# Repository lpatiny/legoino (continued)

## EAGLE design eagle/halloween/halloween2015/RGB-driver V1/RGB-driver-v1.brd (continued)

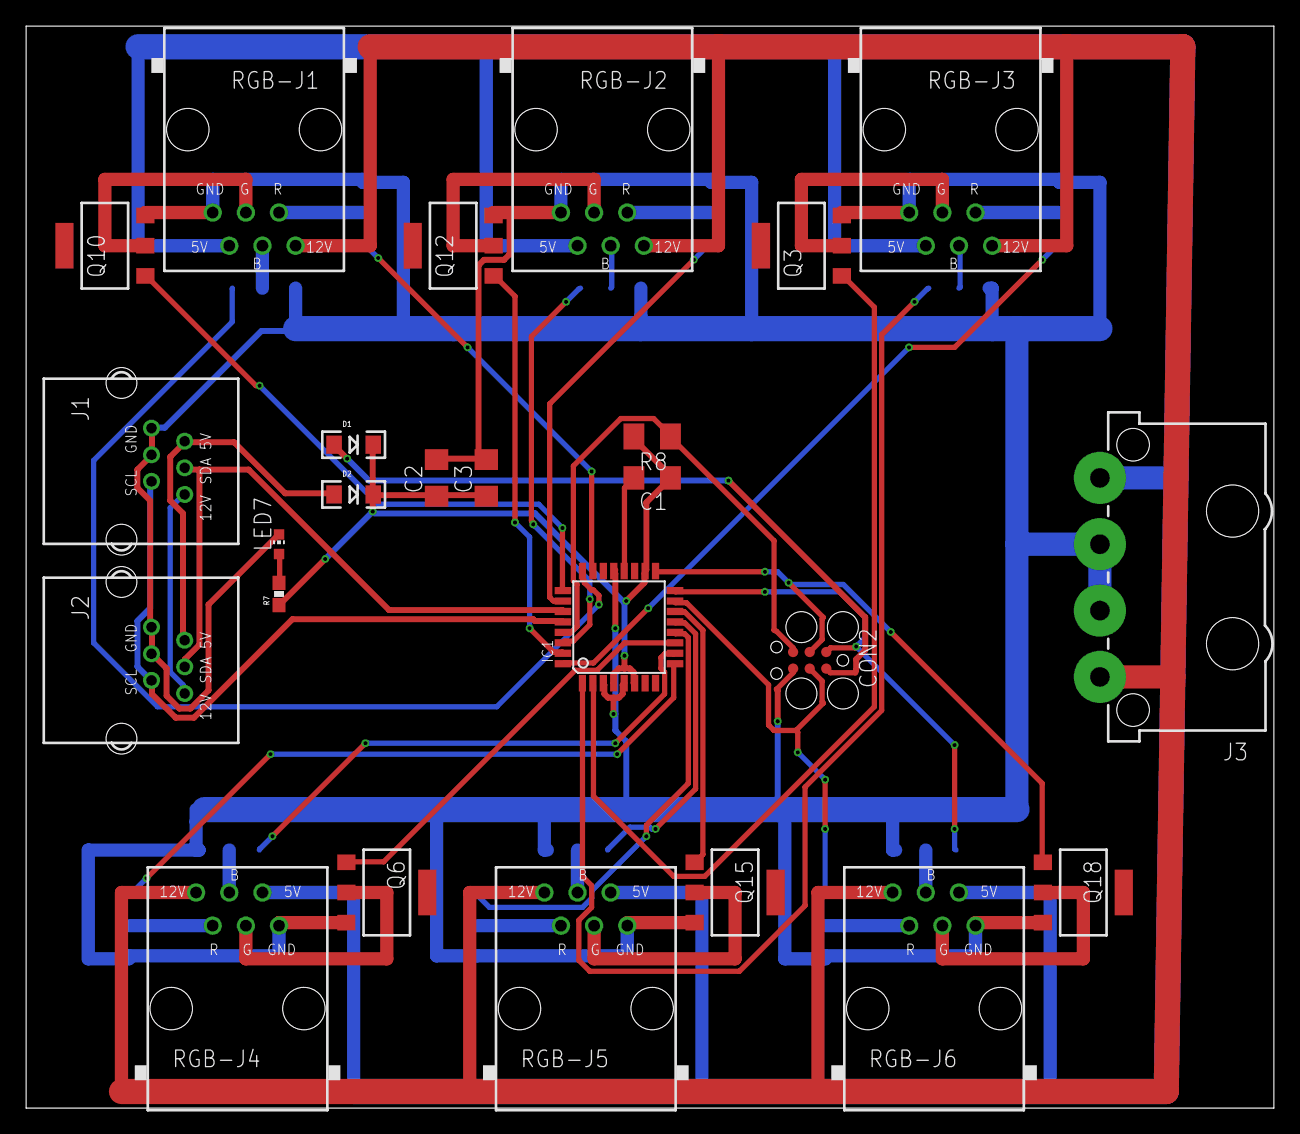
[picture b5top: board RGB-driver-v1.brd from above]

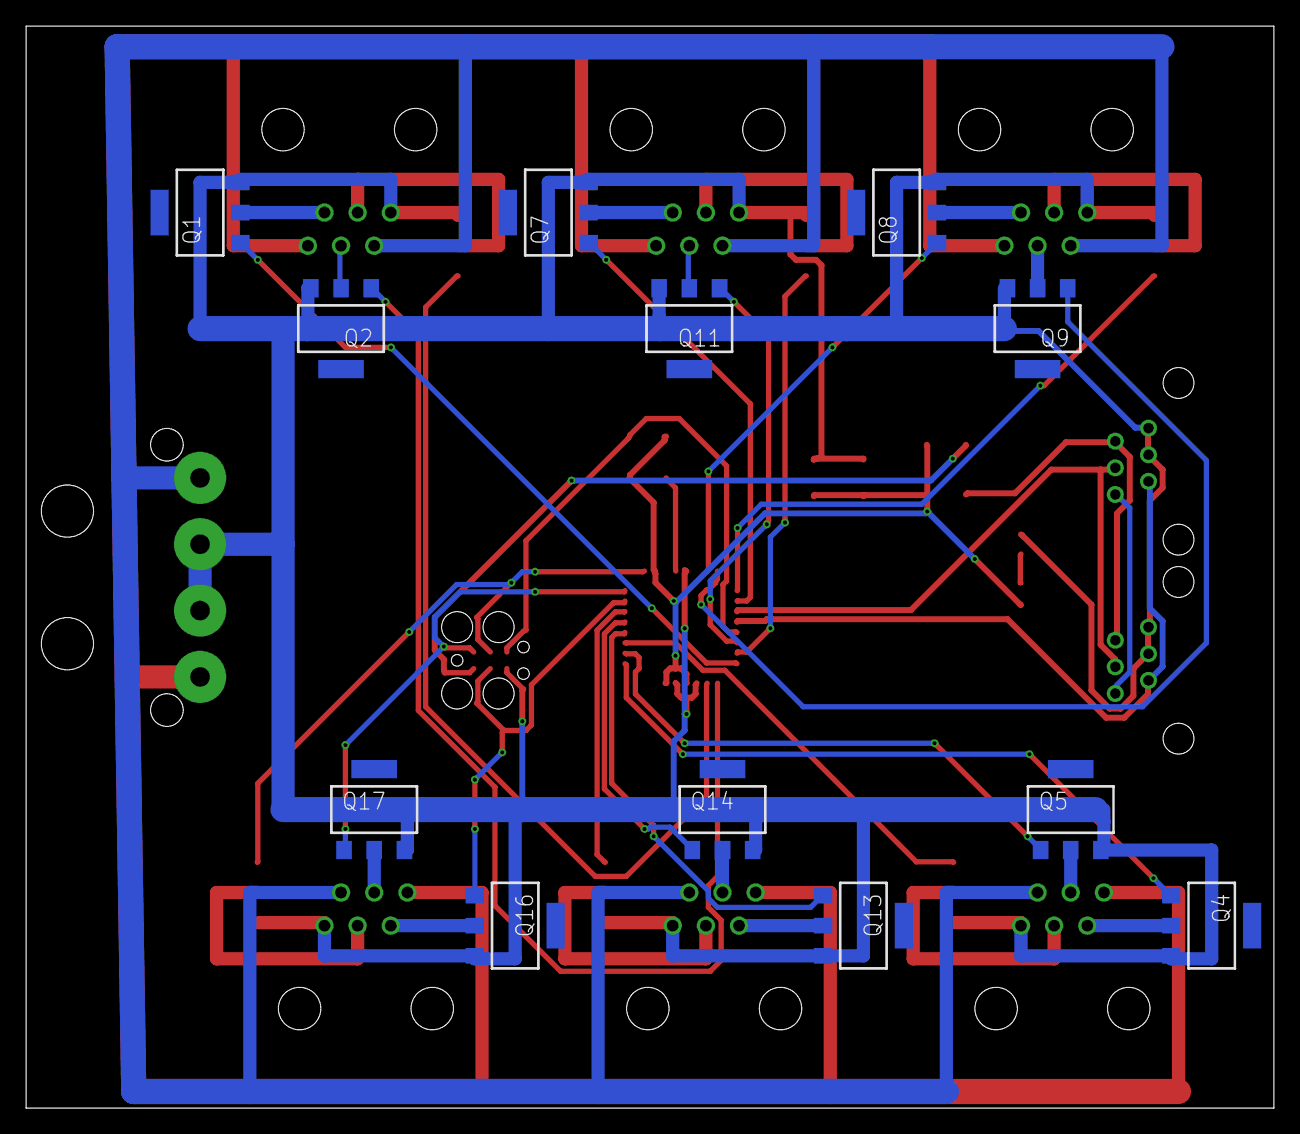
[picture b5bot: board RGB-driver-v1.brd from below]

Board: 2 copper layers, 95.6 x 82.9 mm, 37 parts (12 on the bottom side), 48 nets.

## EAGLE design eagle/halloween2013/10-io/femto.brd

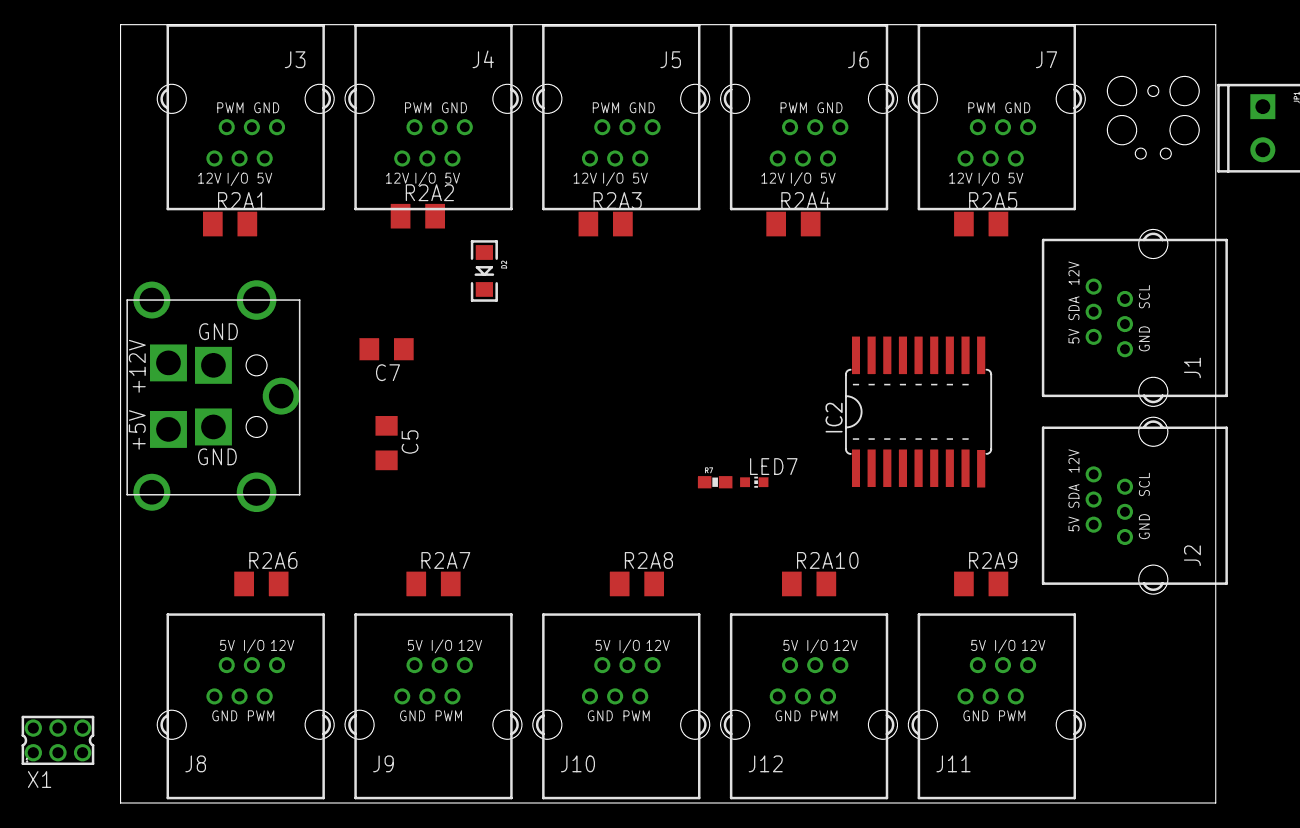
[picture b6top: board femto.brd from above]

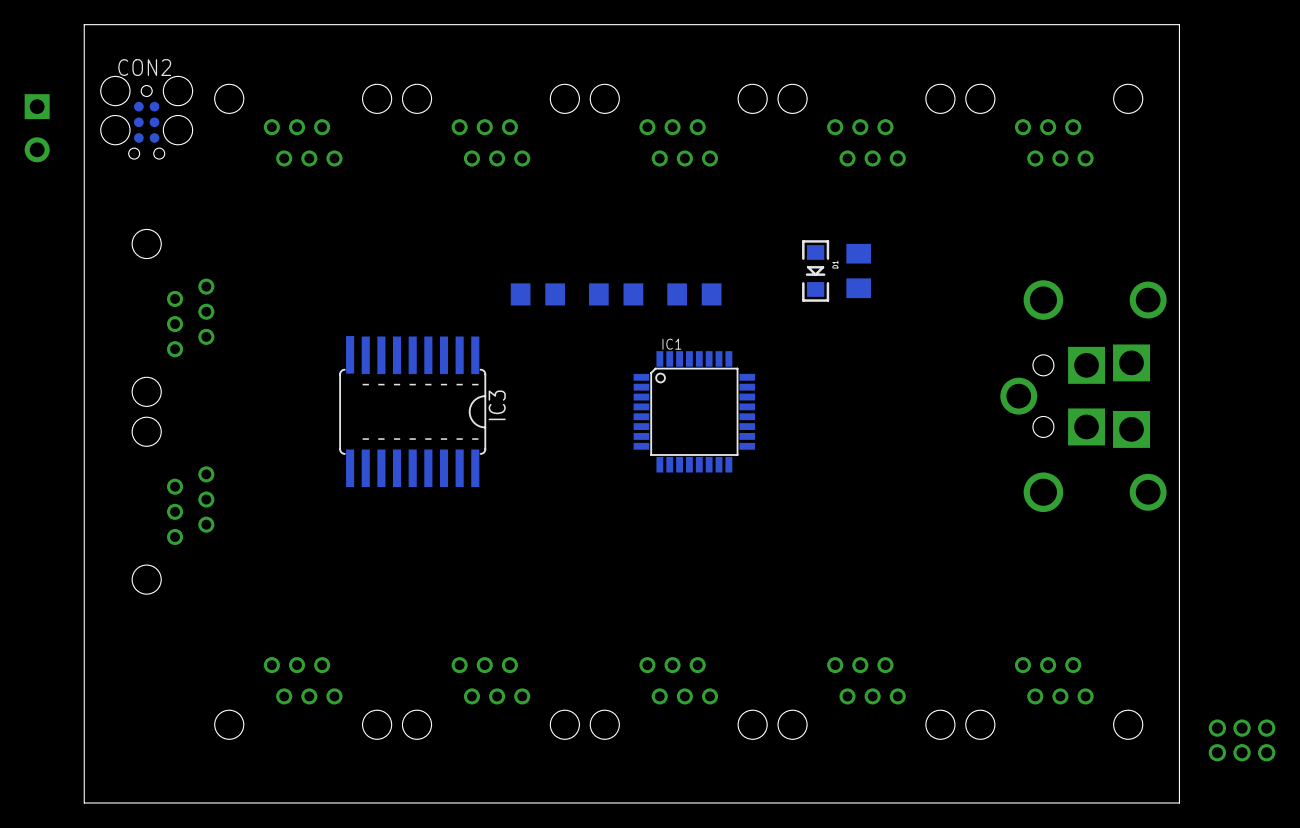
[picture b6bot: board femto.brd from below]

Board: 2 copper layers, 88.9 x 63.2 mm, 39 parts (8 on the bottom side), 45 nets, no tracks yet.

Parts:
C1, C2: 0.1uF; C1206
C3, C5, C7: 10uF; C1206
CON2: TC2030-MCP
D1, D2: 1N581D1206; LED-1206
IC1: MEGA8-AI; TQFP32-08
IC2, IC3: SO18W
J1, J2: RJ12RIGHTANGLE-I2C; RJ12-RIGHTANGLE-I2C
J3, J4, J5, J6, J7, J8, J9, J10, J11, J12: RJ12RIGHTANGLE; RJ12-RIGHTANGLE
JP1: SCREWTERMINAL-3.5MM-2
LED7: CHIP-LED0603
R2A1, R2A2, R2A3, R2A4, R2A5, R2A6, R2A7, R2A8, R2A9, R2A10: 1k; M1206
R7: 10k; 0603-RES
R8: 10k; M1206
U$1: KPJX-4S-S
X1: 87758-0616

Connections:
5V_A: CON2.5V, D1.A
5V_B: J3.+5V, J4.+5V, J5.+5V, J6.+5V, J7.+5V, J8.+5V, J9.+5V, J10.+5V, J11.+5V, J12.+5V, JP1.1
+5V: C1.1, C2.1, C3.1, D1.C, D2.C, IC1.4, IC1.6, IC1.18, R7.1, R8.2
+12V: J3.+12V, J4.+12V, J5.+12V, J6.+12V, J7.+12V, J8.+12V, J9.+12V, J10.+12V, J11.+12V, J12.+12V
A3: IC1.26, R2A1.1, R2A6.1
D2: IC1.32, R2A2.1, R2A7.1
EXT-5V: C5.1, U$1.+5V, X1.1
EXT-12V: C7.2, U$1.+12V, X1.2
GND: C2.2, C3.2, C5.2, C7.1, CON2.GND, IC1.3, IC1.5, IC1.21, IC2.9, IC3.9, J1.GND1, J1.GND2, J2.GND1, J2.GND2, J3.GND1, J3.GND2, J4.GND1, J4.GND2, J5.GND1, J5.GND2, J6.GND1, J6.GND2, J7.GND1, J7.GND2, J8.GND1, J8.GND2, J9.GND1, J9.GND2, J10.GND1, J10.GND2, J11.GND1, J11.GND2, J12.GND1, J12.GND2, JP1.2, LED7.C, U$1.GND1, U$1.GND2
I2C-5V: D2.A, J1.+5V, J2.+5V, X1.5
I2C-12V: J1.+12V, J2.+12V, X1.6
MISO: CON2.MISO, IC1.16, R2A3.1, R2A4.1, R2A5.1, R2A8.1, R2A9.1, R2A10.1
MOSI: CON2.MOSI, IC1.15
unnamed: IC2.1, IC2.2
unnamed: J3.I/O, R2A1.2
unnamed: IC2.17, IC2.18, J3.PWM
unnamed: C1.2, IC1.20
unnamed: IC2.15, IC2.16, J4.PWM
unnamed: IC2.13, IC2.14, J5.PWM
unnamed: IC2.3, IC2.4
unnamed: IC2.5, IC2.6
unnamed: J4.I/O, R2A2.2
unnamed: J5.I/O, R2A3.2
unnamed: IC2.12, J6.PWM
unnamed: J6.I/O, R2A4.2
unnamed: IC2.11, J7.PWM
unnamed: J7.I/O, R2A5.2
unnamed: LED7.A, R7.2
unnamed: IC3.17, IC3.18, J8.PWM
unnamed: IC3.15, IC3.16, J9.PWM
unnamed: IC3.13, IC3.14, J10.PWM
unnamed: J8.I/O, R2A6.2
unnamed: J9.I/O, R2A7.2
unnamed: J10.I/O, R2A8.2
unnamed: IC3.12, J11.PWM
unnamed: J11.I/O, R2A9.2
unnamed: IC3.11, J12.PWM
unnamed: J12.I/O, R2A10.2
unnamed: IC3.1, IC3.2
unnamed: IC3.3, IC3.4
unnamed: IC3.5, IC3.6
RESET: CON2.RESET, IC1.29, R8.1
SCK: CON2.SCK, IC1.17
SCL: IC1.28, J1.SCL, J2.SCL
SDA: IC1.27, J1.SDA, J2.SDA
